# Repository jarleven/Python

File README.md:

# Python
Python introduction for kids

Python kode til bruk på Eid ungdomsskule vinter/vår 2018
http://www.eus.no/

Første prosjekt er ei steg for steg oppskrift for bondesjakk i Python

 bondesjakk-brett.py        - Utskrift av eit brett med 3x3 ruter. Innhold i rutene er henta frå ei liste

 Forsøkslæreplan i valgfag programmering
 https://www.udir.no/kl06/PRG1-01/Hele/Hovedomraader

sudo apt install python-pip

pip install imutils
pip install numpy
pip install cv2
pip install opencv-python
pip install simplecv
pip install pygame
pip install ndimage
pip install scipy
pip install matplotlib
pip install python-tk

pip3 install imutils

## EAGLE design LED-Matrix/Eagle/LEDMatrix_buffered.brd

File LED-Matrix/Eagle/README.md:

### MAX7219 LED Matrix

A schematic starting point

### Schematic (Right click link and select save as)

* [Eagle schematic](https://raw.githubusercontent.com/jarleven/Python/master/LED-Matrix/Eagle/LEDMatrix.sch "download")

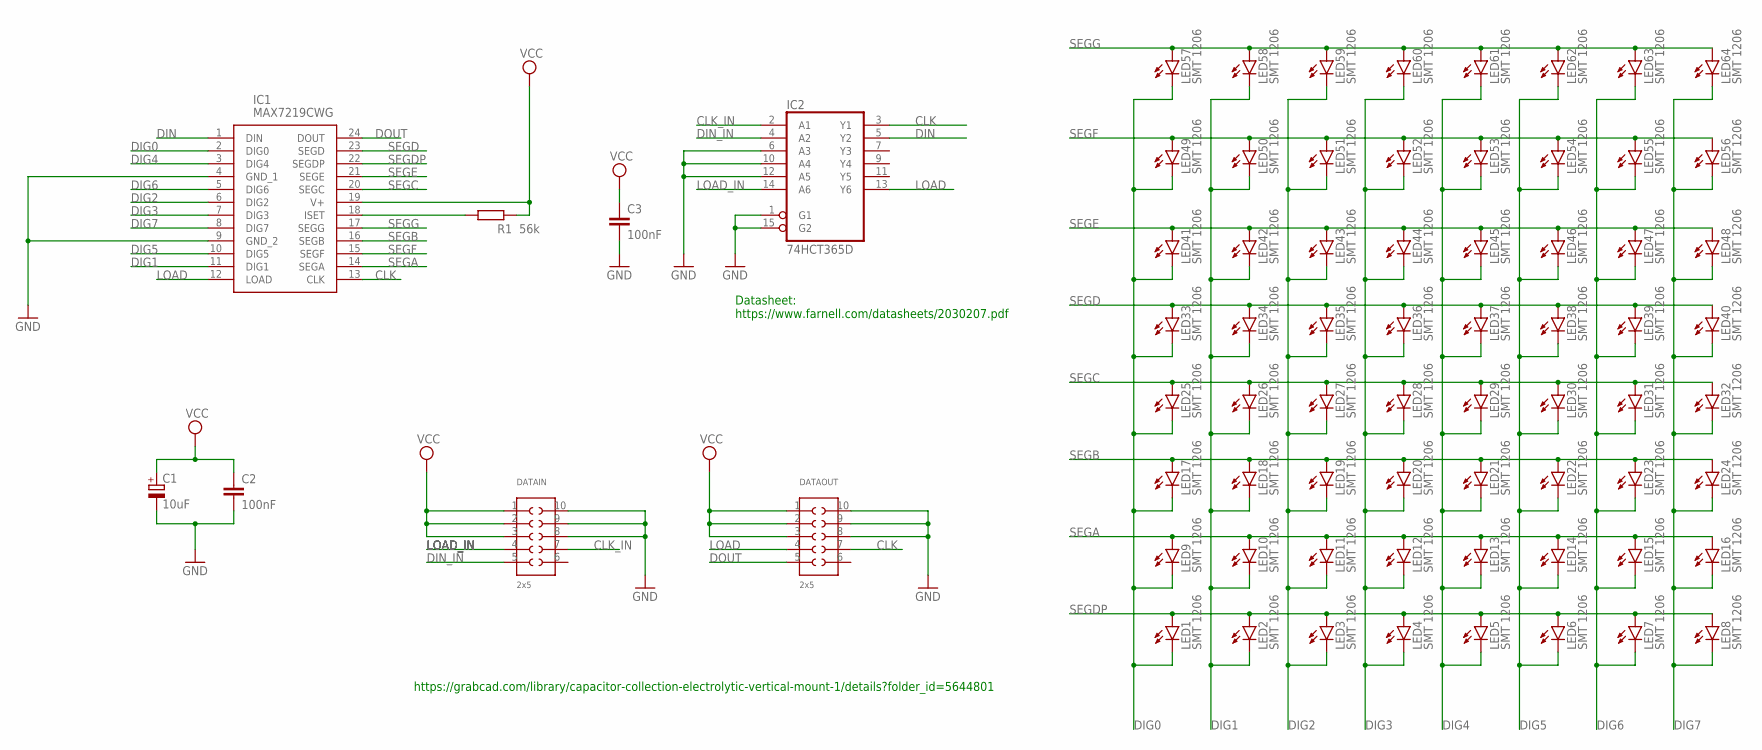
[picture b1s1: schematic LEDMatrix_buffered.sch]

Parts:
C1: 10uF; E5-8,5
C2, C3: 100nF; C1206
DATAIN: 2x5; 610X1021121
DATAOUT: 2x5; 610X1021121
IC1: MAX7219CWG; SOIC127P1032X265-24N
IC2: 74HCT365D; SO16
LED1, LED2, LED3, LED4, LED5, LED6, LED7, LED8, LED9, LED10, LED11, LED12, LED13, LED14, LED15, LED16, LED17, LED18, LED19, LED20, LED21, LED22, LED23, LED24, LED25, LED26, LED27, LED28, LED29, LED30, LED31, LED32, LED33, LED34, LED35, LED36, LED37, LED38, LED39, LED40, LED41, LED42, LED43, LED44, LED45, LED46, LED47, LED48, LED49, LED50, LED51, LED52, LED53, LED54, LED55, LED56, LED57, LED58, LED59, LED60, LED61, LED62, LED63, LED64: SMT 1206; CHIPLED_1206
R1: 56k; R1206

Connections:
CLK: DATAOUT.7, IC1.13 (CLK), IC2.3 (Y1)
CLK_IN: DATAIN.7, IC2.2 (A1)
DIG0: IC1.2 (DIG0), LED1.C, LED9.C, LED17.C, LED25.C, LED33.C, LED41.C, LED49.C, LED57.C
DIG1: IC1.11 (DIG1), LED2.C, LED10.C, LED18.C, LED26.C, LED34.C, LED42.C, LED50.C, LED58.C
DIG2: IC1.6 (DIG2), LED3.C, LED11.C, LED19.C, LED27.C, LED35.C, LED43.C, LED51.C, LED59.C
DIG3: IC1.7 (DIG3), LED4.C, LED12.C, LED20.C, LED28.C, LED36.C, LED44.C, LED52.C, LED60.C
DIG4: IC1.3 (DIG4), LED5.C, LED13.C, LED21.C, LED29.C, LED37.C, LED45.C, LED53.C, LED61.C
DIG5: IC1.10 (DIG5), LED6.C, LED14.C, LED22.C, LED30.C, LED38.C, LED46.C, LED54.C, LED62.C
DIG6: IC1.5 (DIG6), LED7.C, LED15.C, LED23.C, LED31.C, LED39.C, LED47.C, LED55.C, LED63.C
DIG7: IC1.8 (DIG7), LED8.C, LED16.C, LED24.C, LED32.C, LED40.C, LED48.C, LED56.C, LED64.C
DIN: IC1.1 (DIN), IC2.5 (Y2)
DIN_IN: DATAIN.5, IC2.4 (A2)
DOUT: DATAOUT.5, IC1.24 (DOUT)
GND: C1.-, C2.2, C3.2, DATAIN.8, DATAIN.9, DATAIN.10, DATAOUT.8, DATAOUT.9, DATAOUT.10, IC1.4 (GND_1), IC1.9 (GND_2), IC2.1 (G1), IC2.6 (A3), IC2.8 (GND), IC2.10 (A4), IC2.12 (A5), IC2.15 (G2)
LOAD: DATAOUT.4, IC1.12 (LOAD), IC2.13 (Y6)
LOAD_IN: DATAIN.4, IC2.14 (A6)
unnamed: IC1.18 (ISET), R1.1
SEGA: IC1.14 (SEGA), LED9.A, LED10.A, LED11.A, LED12.A, LED13.A, LED14.A, LED15.A, LED16.A
SEGB: IC1.16 (SEGB), LED17.A, LED18.A, LED19.A, LED20.A, LED21.A, LED22.A, LED23.A, LED24.A
SEGC: IC1.20 (SEGC), LED25.A, LED26.A, LED27.A, LED28.A, LED29.A, LED30.A, LED31.A, LED32.A
SEGD: IC1.23 (SEGD), LED33.A, LED34.A, LED35.A, LED36.A, LED37.A, LED38.A, LED39.A, LED40.A
SEGDP: IC1.22 (SEGDP), LED1.A, LED2.A, LED3.A, LED4.A, LED5.A, LED6.A, LED7.A, LED8.A
SEGE: IC1.21 (SEGE), LED41.A, LED42.A, LED43.A, LED44.A, LED45.A, LED46.A, LED47.A, LED48.A
SEGF: IC1.15 (SEGF), LED49.A, LED50.A, LED51.A, LED52.A, LED53.A, LED54.A, LED55.A, LED56.A
SEGG: IC1.17 (SEGG), LED57.A, LED58.A, LED59.A, LED60.A, LED61.A, LED62.A, LED63.A, LED64.A
VCC: C1.+, C2.1, C3.1, DATAIN.1, DATAIN.2, DATAIN.3, DATAOUT.1, DATAOUT.2, DATAOUT.3, IC1.19 (V+), IC2.16 (VCC), R1.2

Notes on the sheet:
https://grabcad.com/library/capacitor-collection-electrolytic-vertical-mount-1/details?folder_id=5644801
Datasheet: https://www.farnell.com/datasheets/2030207.pdf

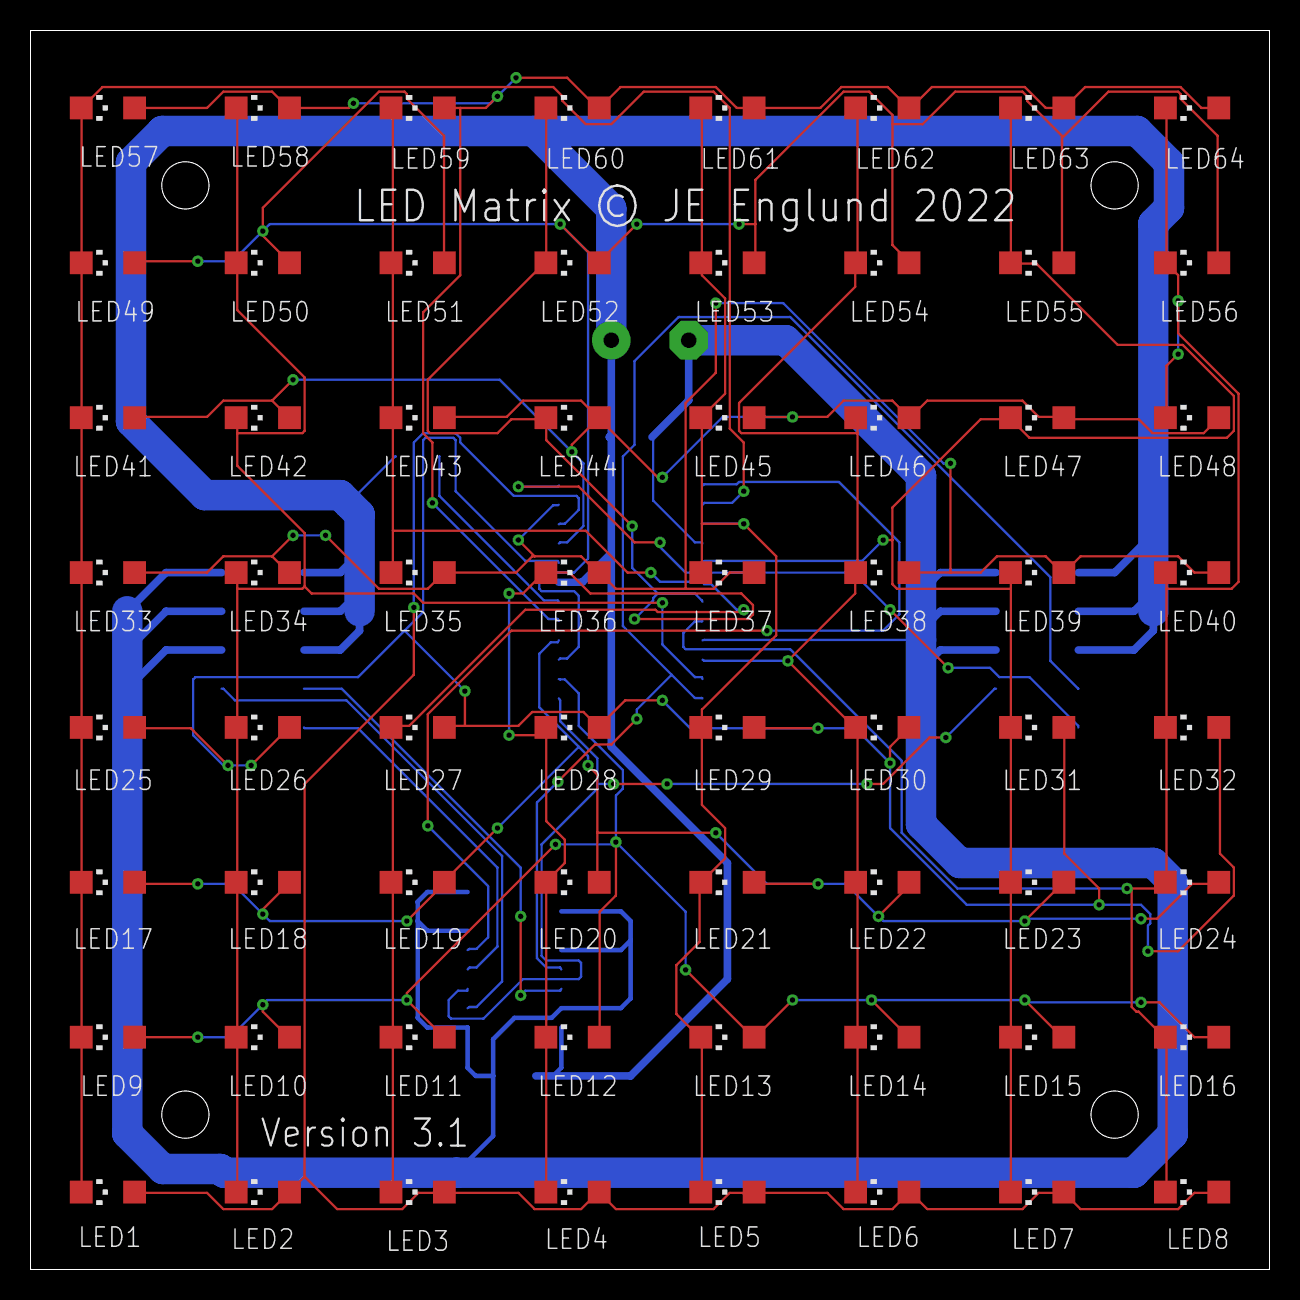
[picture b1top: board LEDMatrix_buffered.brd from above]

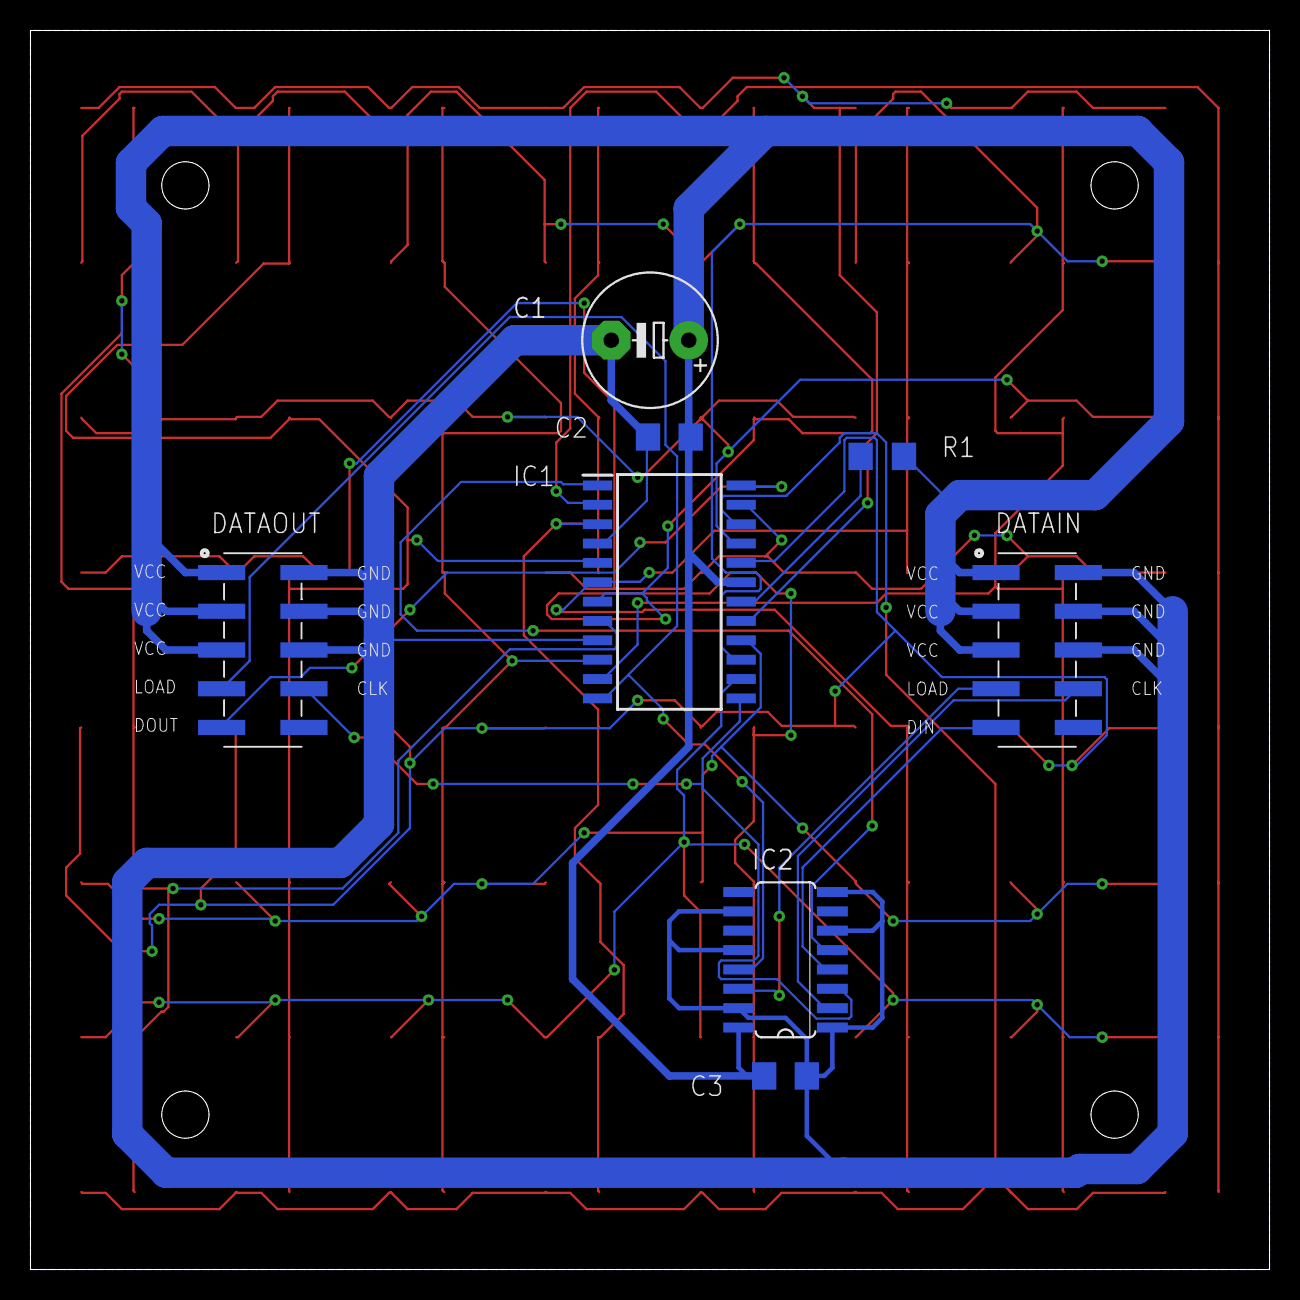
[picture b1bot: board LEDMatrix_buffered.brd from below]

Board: 2 copper layers, 81.3 x 81.3 mm, 72 parts (8 on the bottom side), 26 nets.

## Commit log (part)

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2018-03-20 Delete README2.txt
    Not needed anymore
2018-03-20 Update README.md
    Description
2018-03-20 Update timer.py
    Removed copy paste stuff
2018-03-20 Update timer.py
    Finished!
2018-03-20 Update timer.py
    Renamed a bit
2018-03-20 Update timer.py
    Renaming
2018-03-20 Update timer.py
    Cleanup
2018-03-20 Update timer.py
    Rename
2018-03-20 A screenshot
2018-03-21 Create Square.py
    Draw a rectangle or square in the X,Y plane of the robot axis
2018-03-21 Create GPIO.py
    GPIO example
2018-03-21 Update README.md
    Updated with GPIO example
2018-03-28 Create ThreadsOne.py
    A small thread example
2018-03-28 Create Threads2.py
    Thread example, thread is restarted when it's inactive.
2018-03-28 Rename Threads2.py to ThreadsTwo.py
    Renamed
2018-04-02 New AI example
2018-04-02 Description and pip3 installwq
2018-04-19 Create README.md
    New EV3 repo
2018-04-24 Initial EV3 Dev work
2018-04-24 Added examples of more motor classes
2018-04-24 Added more examples
2018-04-24 More sensors
2018-04-24 More, more examples
2018-04-24 Documentation
2018-04-24 Fixed documentation
2018-04-24 First test
2018-04-25 Removed
2018-04-26 Fixed bad whitespace in file
2018-04-26 Support for Sony module
2018-04-28 Copy files to a temporary directory
2018-04-28 New example with LEDs
2018-04-28 New file
2018-04-28 Small cleanup in comments
2018-05-06 Search still images in EidsElva
2018-05-06 No change
2018-05-07 Fixed for Linux
2018-05-07 In it's simplest form. Play a stream or file or a camera
2018-09-18 Update README.md
    Just some notes when testing again Sep 2018
2018-11-07 Update README.md
    Resolved some questions asked by pupils
2018-11-07 Update Square.py
    Fixed a few things in todays class
2018-11-13 Create README.md
    Initial work
2018-11-14 Update README.md
    Quick test on Ubuntu. Looks like it works like a charm. Only tested wired with USB.
2019-01-05 Create ESP8266.md
    Experimenting with the ESP8266 and MicroPython
2019-01-05 Update ESP8266.md
    Added drawing of the NodeMCU
2019-01-05 Update ESP8266.md
    Onboard LED
2019-01-05 Update ESP8266.md
    Reboot
2019-01-05 Update ESP8266.md
    A simple blink example
2019-01-05 Update ESP8266.md
    First code example
2019-01-05 Update ESP8266.md
    Use the ampy tool
2019-01-05 Update ESP8266.md
    Some words about the files
2019-01-05 Update ESP8266.md
    WiFi basic
2019-01-05 Update ESP8266.md
    Pushbutton example
2019-01-05 Update ESP8266.md
    Network socket
2019-01-05 Update ESP8266.md
    An IRQ callback example
2019-01-05 Update ESP8266.md
    Typo
2019-01-05 Update ESP8266.md
    Working callback code
2019-01-05 Update ESP8266.md
    Ampy info
2019-01-05 Update ESP8266.md
    Advanced example. Need to add some comments
2019-01-06 Update ESP8266.md
    Debounce
2019-01-06 Update ESP8266.md
    Got interrupts on button release. Activated debounce while button is active
2019-01-06 Update ESP8266.md
    Added debounce example
2019-01-07 Update ESP8266.md
    cosmetic
2019-01-07 Create MyTODO.md
    Hacking todo list
2019-02-23 Update ESP8266.md
    Minicom
2019-02-23 Update ESP8266.md
    Minicom baudrate
2019-05-22 Create README.md
    New project
2019-10-08 Update ESP8266.md
    dialout
2019-10-27 Update README.md
    Working example
2019-10-29 Update textScrollLoop.py
    Fixed end of line
2019-10-29 Update readme.md
    Quick setup. Kind of working now
2019-10-29 Update README.md
    Fix formatting of the page
2019-10-29 Update README.md
    Headline
2019-10-29 Update README.md
    ABC
2019-11-08 Create TankRobot.md
    Dump what I have already
2019-11-08 Create HelloWorld.py
    New file
2019-11-08 Update HelloWorld.py
    Simple as it gets
2019-11-08 Update HelloWorld.py
    Comments
2019-11-08 Update README.md
    Howto run
2019-11-10 Update HelloWorld.py
    Added a header from https://github.com/tvierb/raspberry-ascii
2019-11-10 Update HelloWorld.py
    Removed a unused line
2019-11-11 Update HelloWorld.py
    Testing / verifying
2019-11-11 Update HelloWorld.py
    GPIO cleanup
2019-11-11 Update HelloWorld.py
    Print blink
2019-11-11 Update HelloWorld.py
    Apt
2019-11-11 Update HelloWorld.py
    Working
2019-11-11 Update HelloWorld.py
    Handoff
2019-11-11 Update README.md
    Documenting
2019-11-11 Create PollPushbutton.py
    New file
2019-11-11 Create EventPushbutton.py
    New file
2019-11-14 Update README.md
    Added links for further reading
2019-11-14 Update EventPushbutton.py
    Event
2019-12-10 Update README.md
    Cleaned up
2019-12-28 An IoT project
2019-12-28 Loaded on ESP8266
2020-01-03 Garbage collector
2020-01-03 Update main.py
    Added TODO
2020-01-04 Now as a class
2020-01-05 Debug memory and uptime
2020-01-07 Create README.md
    An example
2020-01-25 Update ESP8266.md
    About delay and the watchdog timer
2020-02-24 OLED test
2020-03-17 Added OLED
2020-04-03 Working image over the air
2020-04-04 Simple hack to convert and transfer arbitrary image to the OLED
2020-04-04 Something for later
2020-04-05 Parameter for invert image
2020-04-05 UDP casting to LCD
2020-04-11 Test on fresh machine
2020-12-10 Create Threaded-LEDBlink.py
    Pepperkakehus
2021-01-03 Fire and forget UDP
2021-02-06 Install script
2021-05-02 Rotate display to match hardware layout
2022-02-03 Create README.md
    New descrioption of the LCD luma. Will move from flaskapp soon.
2022-02-04 Create README.md
    Babysteps
2022-02-04 Create setup.sh
    babysteps
2022-02-04 Update setup.sh
    Use PIL
2022-02-04 Update setup.sh
    Worked, but I might have missed some steps in my notes
2022-02-04 Add files via upload
    Copy of https://github.com/Funkrusha/Adafruit_Python_ILI9340/blob/master/examples/image.py
2022-02-04 Update setup.sh
    Load my own version of the image example
2022-02-05 Update setup.sh
    Cleaned up a bit. Not tested at the momet
2022-02-05 Update setup.sh
    One line install. Still not tested after cleanup.
2022-02-05 Update setup.sh
    Refresh is slow "bitbanging" in Python.
2022-02-06 Update setup.sh
    Verified on fresh baked SDCard - works.
2022-02-06 Update image.py
    Drawing example included
2022-02-08 Create ThreadsLumaLCD.py
    Just a mess, but proof of concept
2022-02-13 Update README.md
    Changed library to something tested in the classroom
2022-02-13 Add files via upload
    Moved from the flaskapp repository
2022-02-13 Rename setup_neopixel.py to setup_neopixel.sh
2022-02-13 Update setup_neopixel.sh
    Works both on Bullseye and Buster
2022-02-13 Rename install-luma.sh to setup-luma-emulator.sh
2022-02-13 Update README.md
    Wiring
2022-02-19 Update image.py
    No need to load image from file every time
2022-02-20 Create robodk-hexagon.py
    Copy of the example from RoboDB found @ https://robodk.com/offline-programming
2022-02-23 Add files via upload
    UR10 with RobotiQ camera and gripper
2022-03-13 Add files via upload
    A new go on the pixel remapping. Now using numpy.
2022-11-16 Create lidar.png
    Lidar @ EidVGS
2023-01-03 Sletta fasit
    Detaljar i "Notes"
2023-01-04 Typo and SOIC
    Typo and SOIC
2023-01-04 SOIC and 3D models
2023-01-04 Cleanup
2023-01-04 GitHub link
2023-01-04 The DotMatrix TTF
2023-01-05 Wordfile
2023-01-05 Removed 3D models
2023-01-06 Layers
2023-01-06 Example
2023-01-06 NewRoute
2023-01-06 Zoomed to board only
2023-01-06 New Route
2023-01-06 Zoom
2023-01-11 Lock / Autorouter
2023-01-16 Eksempel
2023-01-17 Numpad for copyright
2023-02-02 MicroPython eksempel
2023-02-05 More working stuff
2023-02-06 Use Matrix as text
2023-02-28 Output from transformation
2023-03-03 PiPico almost copy-paste-example

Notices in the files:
LED-Matrix/Eagle/LEDMatrix_buffered.brd:
LED Matrix © JE Englund 2022
parts and their libraries:
Wurth_Elektronik_Electromechanic_Board_t: Copyright: Würth Elektronik
